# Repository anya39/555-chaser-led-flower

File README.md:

# 555-chaser-led-flower
This is my first PCB project for Hack Club's Stasis.

I used Kicad to create a schematic and route the PCB. I made a flower-shaped 555 LED Chaser board by following the Hack Club Stasis guide and adding my own customizations. 

## 3D view of the finished design on Kicad:

## PCB Price Estimate

## Expected Behavior

When powered with a 5V supply, the NE555 timer operates in astable mode, 
generating a continuous clock signal. The speed of the clock is controlled 
by turning the potentiometer (RV1), which changes the speed of the chasing 
light effect. The CD4017 counter sequences through the 10 outputs (LEDs) to 
light one LED at a time.

## Bill of Materials (BOM)

| Reference | Qty | Value | Footprint | Datasheet | Purchase Link | Price | Notes |
|-----------|-----|-------|-----------|-----------|---------------|-------|-------|
| C3 | 1 | 0.01 uF | Capacitor_THT:C_Disc_D7.5mm_W2.5mm_P5.00mm | - | [DigiKey](https://www.digikey.com/en/products/detail/kemet/C320C103K3G5TA/6656406) | $0.56 | |
| C4 | 1 | 1 uF | Capacitor_THT:CP_Radial_D5.0mm_P2.00mm | - | [DigiKey](https://www.digikey.com/en/products/detail/w%C3%BCrth-elektronik/860020672005/5727088) | $0.10 | |
| D1-D10 | 10 | LED | LED_THT:LED_D3.0mm | - | [DigiKey](https://www.digikey.com/en/products/detail/w%C3%BCrth-elektronik/151031VS06000/4489988) | $0.17 | |
| J1 | 1 | Conn_01x02_Socket | Connector_PinHeader_2.54mm:PinHeader_1x02_P2.54mm_Vertical | - | [DigiKey](https://www.digikey.com/en/products/detail/te-connectivity-amp-connectors/215297-2/2055922) | $0.95 | |
| J2 | 1 | Conn_01x01_Socket | Connector_PinHeader_2.54mm:PinHeader_1x01_P2.54mm_Vertical | - | [DigiKey](https://www.digikey.com/en/products/detail/adam-tech/RS1-02-G/9832044) | $0.20 | Break off 1 pin from strip |
| R1 | 1 | 1kΩ | Resistor_THT:R_Axial_DIN0204_L3.6mm_D1.6mm_P7.62mm_Horizontal | - | [DigiKey](https://www.digikey.com/en/products/detail/te-connectivity-passive-product/YR1B1K0CC/2390772) | $0.84 | |
| R3 | 1 | 470Ω | Resistor_THT:R_Axial_DIN0207_L6.3mm_D2.5mm_P7.62mm_Horizontal | - | [DigiKey](https://www.digikey.com/en/products/detail/stackpole-electronics-inc/CF14JT470R/1741440) | $0.10 | |
| RV1 | 1 | 50kΩ | Potentiometer_THT:Potentiometer_Vishay_T93YA_Vertical | - | [DigiKey](https://www.digikey.com/en/products/detail/vishay-sfernice/T93YA503KT20/1587723) | $1.85 | |
| U1 | 1 | NE555P | Package_DIP:DIP-8_W7.62mm | [Datasheet](http://www.ti.com/lit/ds/symlink/ne555.pdf) | [DigiKey](https://www.digikey.com/en/products/detail/texas-instruments/NE555P/277057) | $0.51 | |
| U2 | 1 | CD4017BE | custom_imports:N16 | [Datasheet](http://www.intersil.com/content/dam/Intersil/documents/cd40/cd4017bms-22bms.pdf) | [DigiKey](https://www.digikey.com/en/products/detail/texas-instruments/CD4017BE/67253) | $1.27 | |

**Estimated Components Total When Bought Individually: ~$6.55** (excluding shipping and tax)

**Estimated PCB Total (with payment fee, excluding shipping and tax): $2.50**

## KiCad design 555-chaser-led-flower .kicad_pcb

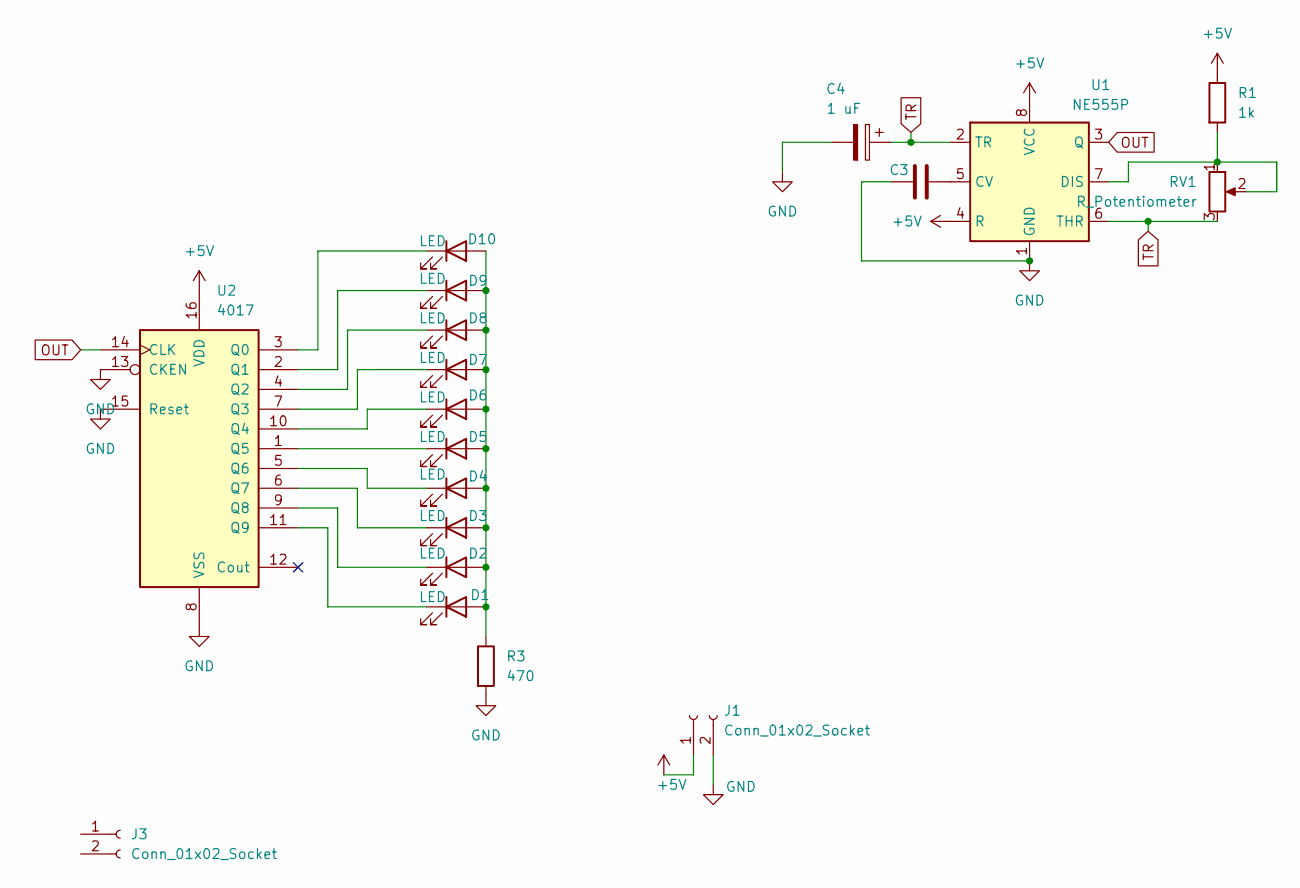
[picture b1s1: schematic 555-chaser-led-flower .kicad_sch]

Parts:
C3: 0.01 uF; C_Disc_D7.5mm_W2.5mm_P5.00mm
C4: 1 uF; CP_Radial_D5.0mm_P2.00mm
D1, D2, D3, D4, D5, D6, D7, D8, D9, D10: LED; LED_D3.0mm
J1, J3: Conn_01x02_Socket; PinHeader_1x02_P2.54mm_Vertical
R1: 1k; R_Axial_DIN0204_L3.6mm_D1.6mm_P7.62mm_Horizontal
R3: 470; R_Axial_DIN0207_L6.3mm_D2.5mm_P7.62mm_Horizontal
RV1: R_Potentiometer; Potentiometer_Vishay_T93YA_Vertical
U1: NE555P; DIP-8_W7.62mm
U2: 4017; N16

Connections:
+5V: J1.1, R1.1, U1.4 (R), U1.8 (VCC), U2.16 (VDD)
GND: C3.1, C4.2, J1.2, R3.2, U1.1 (GND), U2.8 (VSS), U2.13 (CKEN), U2.15 (Reset)
unnamed: D1.2 (A), D2.2 (A), D3.2 (A), D4.2 (A), D5.2 (A), D6.2 (A), D7.2 (A), D8.2 (A), D9.2 (A), D10.2 (A), R3.1
unnamed: D1.1 (K), U2.11 (Q9)
unnamed: D2.1 (K), U2.9 (Q8)
unnamed: D3.1 (K), U2.6 (Q7)
unnamed: D4.1 (K), U2.5 (Q6)
unnamed: D5.1 (K), U2.1 (Q5)
unnamed: D6.1 (K), U2.10 (Q4)
unnamed: D7.1 (K), U2.7 (Q3)
unnamed: D8.1 (K), U2.4 (Q2)
unnamed: D9.1 (K), U2.2 (Q1)
unnamed: D10.1 (K), U2.3 (Q0)
unnamed: C3.2, U1.5 (CV)
unnamed: R1.2, RV1.1, RV1.2, U1.7 (DIS)
OUT: U1.3 (Q), U2.14 (CLK)
TR: C4.1, RV1.3, U1.2 (TR), U1.6 (THR)

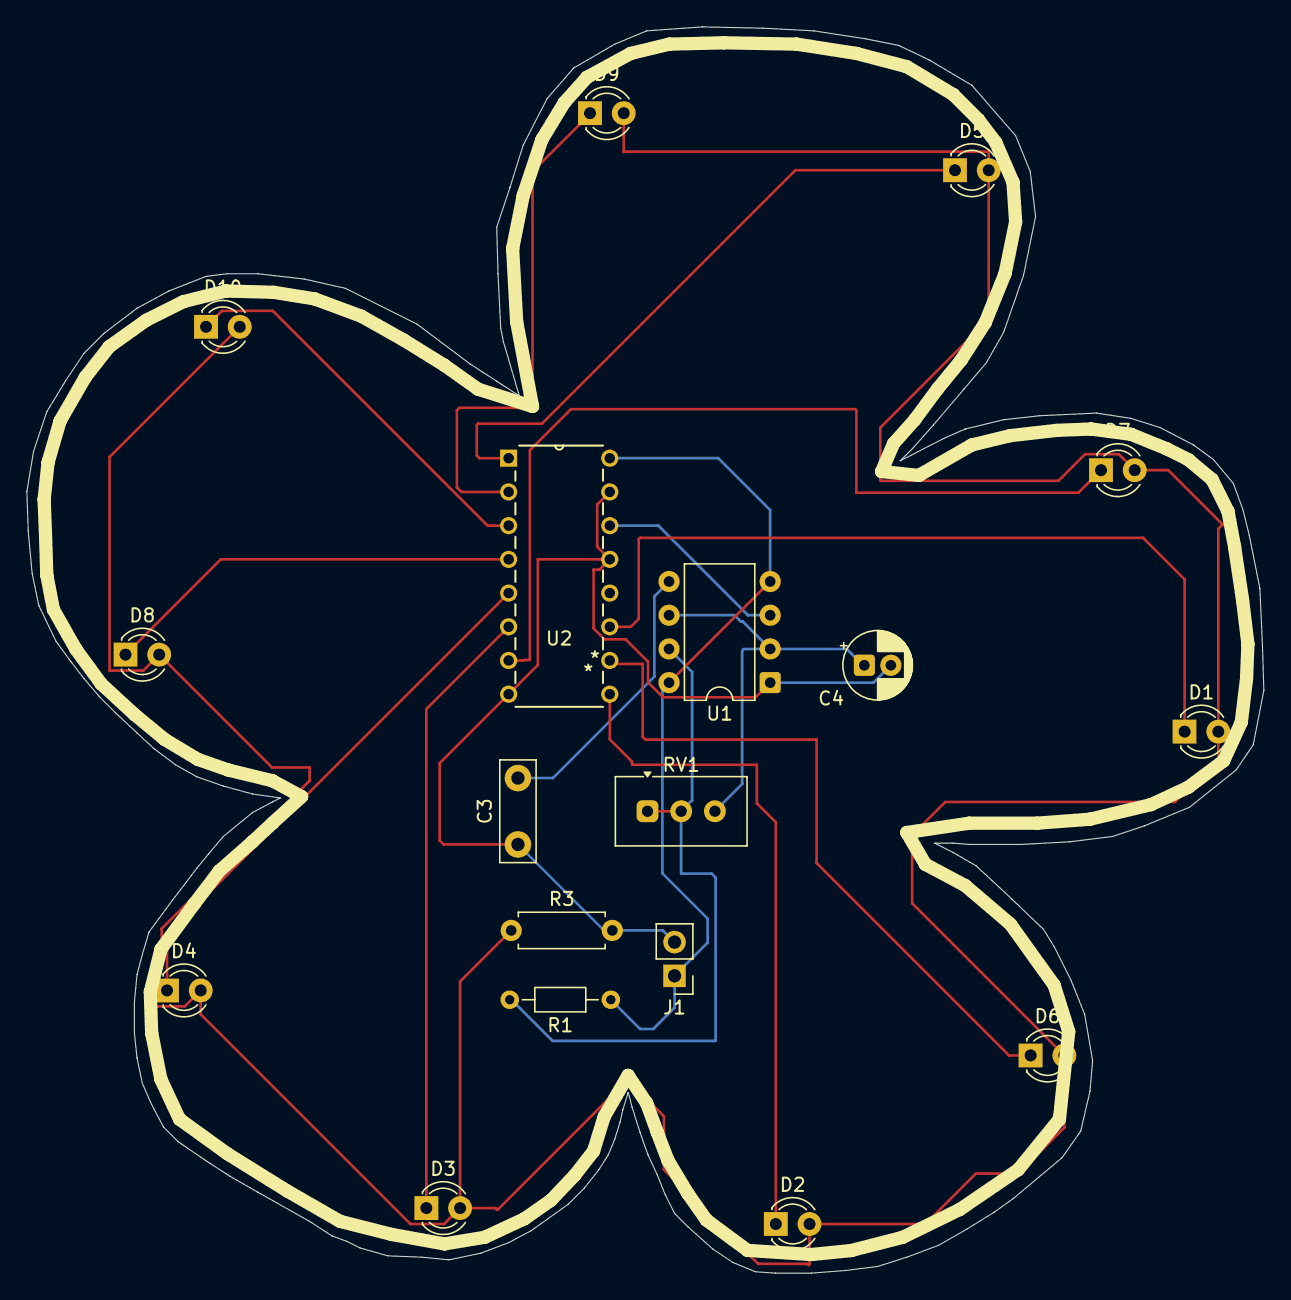
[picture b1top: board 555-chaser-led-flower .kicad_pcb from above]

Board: 2 copper layers, 93.2 x 93.9 mm, 18 parts (0 on the bottom side), 17 nets.

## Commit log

2026-05-04 readme updates
    Expanded project description and added details about the design process and customizations.
2026-05-04 Delete 555-chaser-led-flower .kicad_pcb
    because i fixed errors and need to update all files
2026-05-04 Delete 555-chaser-led-flower .kicad_pro
    because i fixed errors and need to update all files
2026-05-04 Delete 555-chaser-led-flower .kicad_sch
    because i fixed errors and need to update all files
2026-05-04 Delete Screenshot 2026-05-03 at 8.02.44 PM.png
    because i fixed errors and need to update all files
2026-05-04 Delete gerbers.zip
    because i fixed errors and need to update all files
2026-05-04 Add new image to README for 3D view
    Added a new image of the finished design to the README.
2026-05-04 uploaded all updated files
2026-05-06 BOM cvs
2026-05-07 pcb folder
2026-05-07 Create pcb folder
2026-05-07 Create pcb
2026-05-07 Add hardware folder
2026-05-07 pcb, sch, and pro files
2026-05-07 production folder
2026-05-07 gerber folder
2026-05-07 gerbers.zip upload
2026-05-07 docs folder
2026-05-07 screenshots of pcb and schematic
2026-05-07 Add BOM section to README
2026-05-07 Remove BOM section from README
    Removed BOM section from README.md.
2026-05-09 readme update
2026-05-09 BOM with purchase links and prices
2026-05-09 updated BOM
2026-05-09 updated footprints in BOM
2026-05-09 added expected behavior to readme
2026-05-09 JLCPCB price estimate to readme
2026-05-14 new gerber.zip file
2026-05-14 new kicad pcb files
2026-05-14 updated pcb layout screenshot
2026-05-15 price update in readme
2026-05-15 formatting update
2026-05-15 formatting
